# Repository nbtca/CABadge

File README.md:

# CABadge · 计协电子吧唧

基于 ESP32-S3 的开源圆屏电子徽章，面向日常佩戴与社团展示。用静态或动态壁纸表达个人喜好，通过触摸切换协会名片和小应用，也可以通过电脑或无线连接管理内容。

[固件下载](https://github.com/nbtca/CABadge/releases/tag/v1.2.0) · [PCB 工程](hardware/pcb/current/README.md) · [外壳文件](hardware/enclosure/releases/V11_V2_1_20261020/README.md) · [使用与复刻](docs/REPRODUCE.md)

<p align="center">
  
  <br />
  <sub>圆屏亮屏实物 · 计协图案</sub>
</p>

<table align="center">
  <tr>
    <td align="center"><br /><sub>侧边按键与边框</sub></td>
    <td align="center"><br /><sub>侧面轮廓</sub></td>
  </tr>
</table>

照片展示外观与亮屏效果，点击可查看原图；设计版本与验证状态见[下方版本表](#版本与资料对应)。

## 可以做什么

- **壁纸与名片**：静态图片、EAF 动态壁纸、协会名片，支持触摸浏览和切换。
- **内容管理**：通过 USB 或本地 HTTP 上传壁纸，支持 Wi-Fi、BLE 连接管理；电脑端提供原生 NBTCA Badge TOOL。
- **日常交互**：亮度设置、姿态与唤醒交互、可选 FPS 显示。
- **小应用**：Grok 表情、MC 二维地图、奶蛙矿工、重力小球，以及测试版中的 FluidBox、TimeTiles 和 BLE 心率。详见[应用说明](firmware-v7/APPS.md)。

GIF/视频需先在电脑端转换为 EAF，设备不直接播放 GIF/视频。OTA 与 BLE 传图尚未提供；功能适用版本及待测项见[已知问题](docs/KNOWN_ISSUES.md)。

## 快速入口

| 你想做什么 | 从这里开始 |
| --- | --- |
| 已有设备，安装或使用固件 | [正式固件](https://github.com/nbtca/CABadge/releases/tag/v1.2.0)、[测试固件](https://github.com/nbtca/CABadge/releases/tag/v1.3.0-rc.1)、[安装步骤](docs/REPRODUCE.md#5-烧录所选版本固件)、[无线与壁纸管理](firmware-v7/usb_screen/README.md) |
| 自己制作一块 CABadge | [V2.1 PCB](hardware/pcb/current/README.md)、[BOM 与采购资料](hardware/bom/README.md)、[V11 外壳与装配](hardware/enclosure/releases/V11_V2_1_20261020/README.md)、[完整复刻流程](docs/REPRODUCE.md) |
| 查看单个应用源码 | [应用源码目录](apps/README.md)：宝可梦、TimeTiles、Grok、MC 实时地图，各自单独保存 |
| 修改源码或参与开发 | [构建环境](docs/BUILD.md)、[开发约定](docs/DEVELOPMENT.md)、[界面架构](docs/architecture/UI_ARCHITECTURE_V7.md) |

## 版本与资料对应

固件、PCB 与外壳独立编号，请按用途选择配套文件。

| 资料 | 当前版本 | 下载或说明 |
| --- | --- | --- |
| 正式固件 | v1.2.0 / 7.9.16-eaf-transition | [正式 Release](https://github.com/nbtca/CABadge/releases/tag/v1.2.0)，工作台默认安装此版 |
| 测试固件 | v1.3.0-rc.1 / 7.9.23-timetiles-fix | [测试 Release](https://github.com/nbtca/CABadge/releases/tag/v1.3.0-rc.1)，新功能仍有待测项 |
| 公开源码 | [7.9.23-timetiles-fix](firmware-v7/version.json) | `main` 分支；[自行编译](docs/BUILD.md) |
| 当前 PCB | V2.1 GEK100 / 星火计划 | [工程说明](hardware/pcb/current/README.md)：[嘉立创EDA原生重画版](hardware/pcb/current/easyeda/CABadge_V2_1_GEK100.epro2)（2026-10-27）与 [KiCad 原工程](hardware/pcb/current/kicad/CABadge_V2_1.kicad_pro)（2026-10-20），两者不自动同步 |
| 配套外壳 | V11 一体杯壳 + V11_Button_R2 | [打印件与装配](hardware/enclosure/releases/V11_V2_1_20261020/README.md)、[SolidWorks / STEP](https://github.com/nbtca/CABadge/releases/tag/enclosure-v11-cup-button-20261029)；仅 Cup + Button，按键专项待验证 |
| 历史硬件 | V1 首板 c7c59dff，仅 KiCad | [V1 归档](hardware/pcb/archive/V1_c7c59dff/README.md)；冻结制造包属于此版 |

**自行编译请使用 `main`。** `v1.3.0-rc.1` 标签的自动 `Source code (zip)` 是旧源码快照，与其 7.9.23 固件附件不对应；[下载说明](docs/REPRODUCE.md#1-下载固件与配套硬件)解释各文件的用途。

首板 c7c59dff 的实测证据见[首板测试记录](首板测试记录.md)。V2.1 新增电源与机构、R2 按钮，以及测试固件的部分交互和长稳仍需分项验证；照片、构建或 CAD 检查不代表这些项目已全部通过。

## 硬件概览

| 部分 | 设计规格 |
| --- | --- |
| 主控与存储 | ESP32-S3R8，8 MB Octal PSRAM；W25Q128JVSIQ，16 MB Flash |
| 显示与输入 | 360 × 360 圆形 ST77916 屏幕、触摸输入、SC7A20 运动传感器 |
| 电源与充电 | SGM62117 升降压至 3.3 V；TP4056-MS 及外围供电分配、充电使能电路 |
| PCB | 直径 50 mm、四层板、名义板厚 1.6 mm |

## 如何开始复刻

1. **选定版本**：从上方表格分别选择 PCB、外壳与固件。
2. **准备器件和板子**：按[BOM 说明](hardware/bom/README.md)核对采购，从所选 PCB 工程导出并检查制造文件。
3. **焊接与上电**：按[分阶段检查表](焊接与分阶段上电检查_首板.md)调试；V2.1 新增电路的检查要求见[完整复刻说明](docs/REPRODUCE.md#4-分阶段焊接与首次上电)。
4. **安装固件**：按[烧录步骤](docs/REPRODUCE.md#5-烧录所选版本固件)核对版本、备份需要的数据并安装；已有同版设备可从这一步开始。
5. **验证与装配**：检查显示、触摸、壁纸及连接，再按[外壳装配说明](hardware/enclosure/releases/V11_V2_1_20261020/ASSEMBLY.md)完成组装。

BOM 保留 `DRAFT` 状态；V2.1 尚未附配套制造 ZIP，需从实际选用的工程导出。V1 冻结制造包不能用于制作 V2.1。具体器件、打样、分区及升级注意事项见[复刻与安装](docs/REPRODUCE.md)。

## 继续开发

板端使用 ESP-IDF / PlatformIO 与 LVGL 9.4.0，当前构建流程面向 Windows、Python 3.10+ 和 PowerShell 7。环境由 `tools/bootstrap.ps1` 安装；`CABADGE_BUILD_ROOT` 可配置工具目录，默认 `F:\CABadgeBuild`。详细操作见[构建说明](docs/BUILD.md)与[开发约定](docs/DEVELOPMENT.md)。

| 目录 | 内容 |
| --- | --- |
| `firmware-v7/` | 公开固件、UI、工作台、协议与宿主检查 |
| `hardware/` | PCB 工程、V1 归档、BOM、制造包与外壳 |
| `tools/` | 环境安装、烧录、仓库检查与发布工具 |
| `docs/` | 使用、复刻、构建、架构及已知问题 |

[完整文档索引](docs/INDEX.md) · [已知问题](docs/KNOWN_ISSUES.md) · [第三方来源与许可](docs/THIRD_PARTY.md)

## 致谢

感谢 **[嘉立创](https://www.jlc.com/)** 和 **[华秋](https://www.hqpcb.com/)** 提供的免费打板支持，也感谢组织成员 **[m1ngsama](https://github.com/m1ngsama)** 提供的 Pro 账号。这些支持为本项目的开发提供了极大的帮助。

## 许可

本项目原创内容采用 [MIT License](LICENSE)。第三方字体、库、模型和素材仍遵循各自许可；字体许可见 [FONT-LICENSE.txt](firmware-v7/ui/FONT-LICENSE.txt)。

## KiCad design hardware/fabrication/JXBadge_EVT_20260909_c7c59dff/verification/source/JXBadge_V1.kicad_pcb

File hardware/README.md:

# CABadge 硬件资料

**当前板卡：V2.1 GEK100 / 星火计划。** [打开当前版本说明](pcb/current/README.md)，选择 [KiCad 工程](pcb/current/kicad/CABadge_V2_1.kicad_pro)或[嘉立创EDA工程](pcb/current/easyeda/CABadge_V2_1_GEK100.epro2)。

| 版本 | 格式与来源 | 入口 |
| --- | --- | --- |
| 当前 V2.1 | KiCad 保留 2026-10-20 原文件；EDA 替换为 2026-10-27 原生重画工程 | [pcb/current](pcb/current/README.md) |
| V1 首板 c7c59dff | 仅 KiCad，连同原理图、项目库和模型归档 | [pcb/archive/V1_c7c59dff](pcb/archive/V1_c7c59dff/README.md) |

今天的重画工程属于 V2.1 的 EDA 格式更新，五张原理图复用、PCB 原生重画。旧的 KiCad 转换版 EDA 已从当前仓库文件中移除，过往版本由 Git 历史保留。

## 目录与使用范围

| 目录 | 内容 | 版本说明 |
| --- | --- | --- |
| [pcb/current](pcb/current/README.md) | 当前 V2.1 的 KiCad、EDA、预览与校验信息 | 后续 V2.1 工程更新使用固定路径 |
| [V1 归档](pcb/archive/V1_c7c59dff/README.md) | 首板 KiCad 源文件、符号库、封装库和本地模型 | 历史源文件；与冻结制造快照分别保存 |
| [bom](bom/README.md) | 原 BOM、采购表、料号列表、版本对比及交互式 BOM | CSV 为已有 V1 / V2.1 KiCad 用量记录；交互式 BOM 为 V1 快照，元器件核对已停止 |
| [冻结制造包](fabrication/JXBadge_EVT_20260909_c7c59dff/下单说明.md) | 首板 Gerber、钻孔、钢网及导出核验源快照 | 本次保持路径与全部文件字节不变 |
| [V11 外壳](enclosure/releases/V11_V2_1_20261020/README.md) | V2.1 配套打印件、装配模型与说明；当前按钮为 R2 | 2026-10-29 按实际装配更新为 Cup + Button 两件打印方案，杯壳与 R2 按帽几何保持；几何检查对应说明中的 KiCad PCB；[V6](enclosure/releases/V6_20260930/README.md)为历史外壳 |

## 采购、装配与验证

当前 EDA 中 J1 为 AFC07-S18ECC-00 / C2840708，按用户决定保留原封装；U3 保持 SC7A20TR / C5126709。BOM 和商城器件库核对已停止，旧 CSV 未在本次整理中重新核对或改料。

电池沿用用户提供的 450 mAh、42×30×4 mm，正负线直接焊接、J3 不装。具体版本和历史装配说明见 [BOM 说明](bom/README.md)、[J1 更正](../docs/J1-CONNECTOR.md)和[V1 历史记录](pcb/archive/V1_c7c59dff/README.md#电池与屏幕连接器)。

[焊接与分阶段上电检查](../焊接与分阶段上电检查_首板.md)保留其设计核对依据；[首板测试记录](../首板测试记录.md)保留实物反馈与历史失败。工程归档、文件校验及已有 CAD 检查不代替 V2.1 新板的制造、机械和实物功能验收。

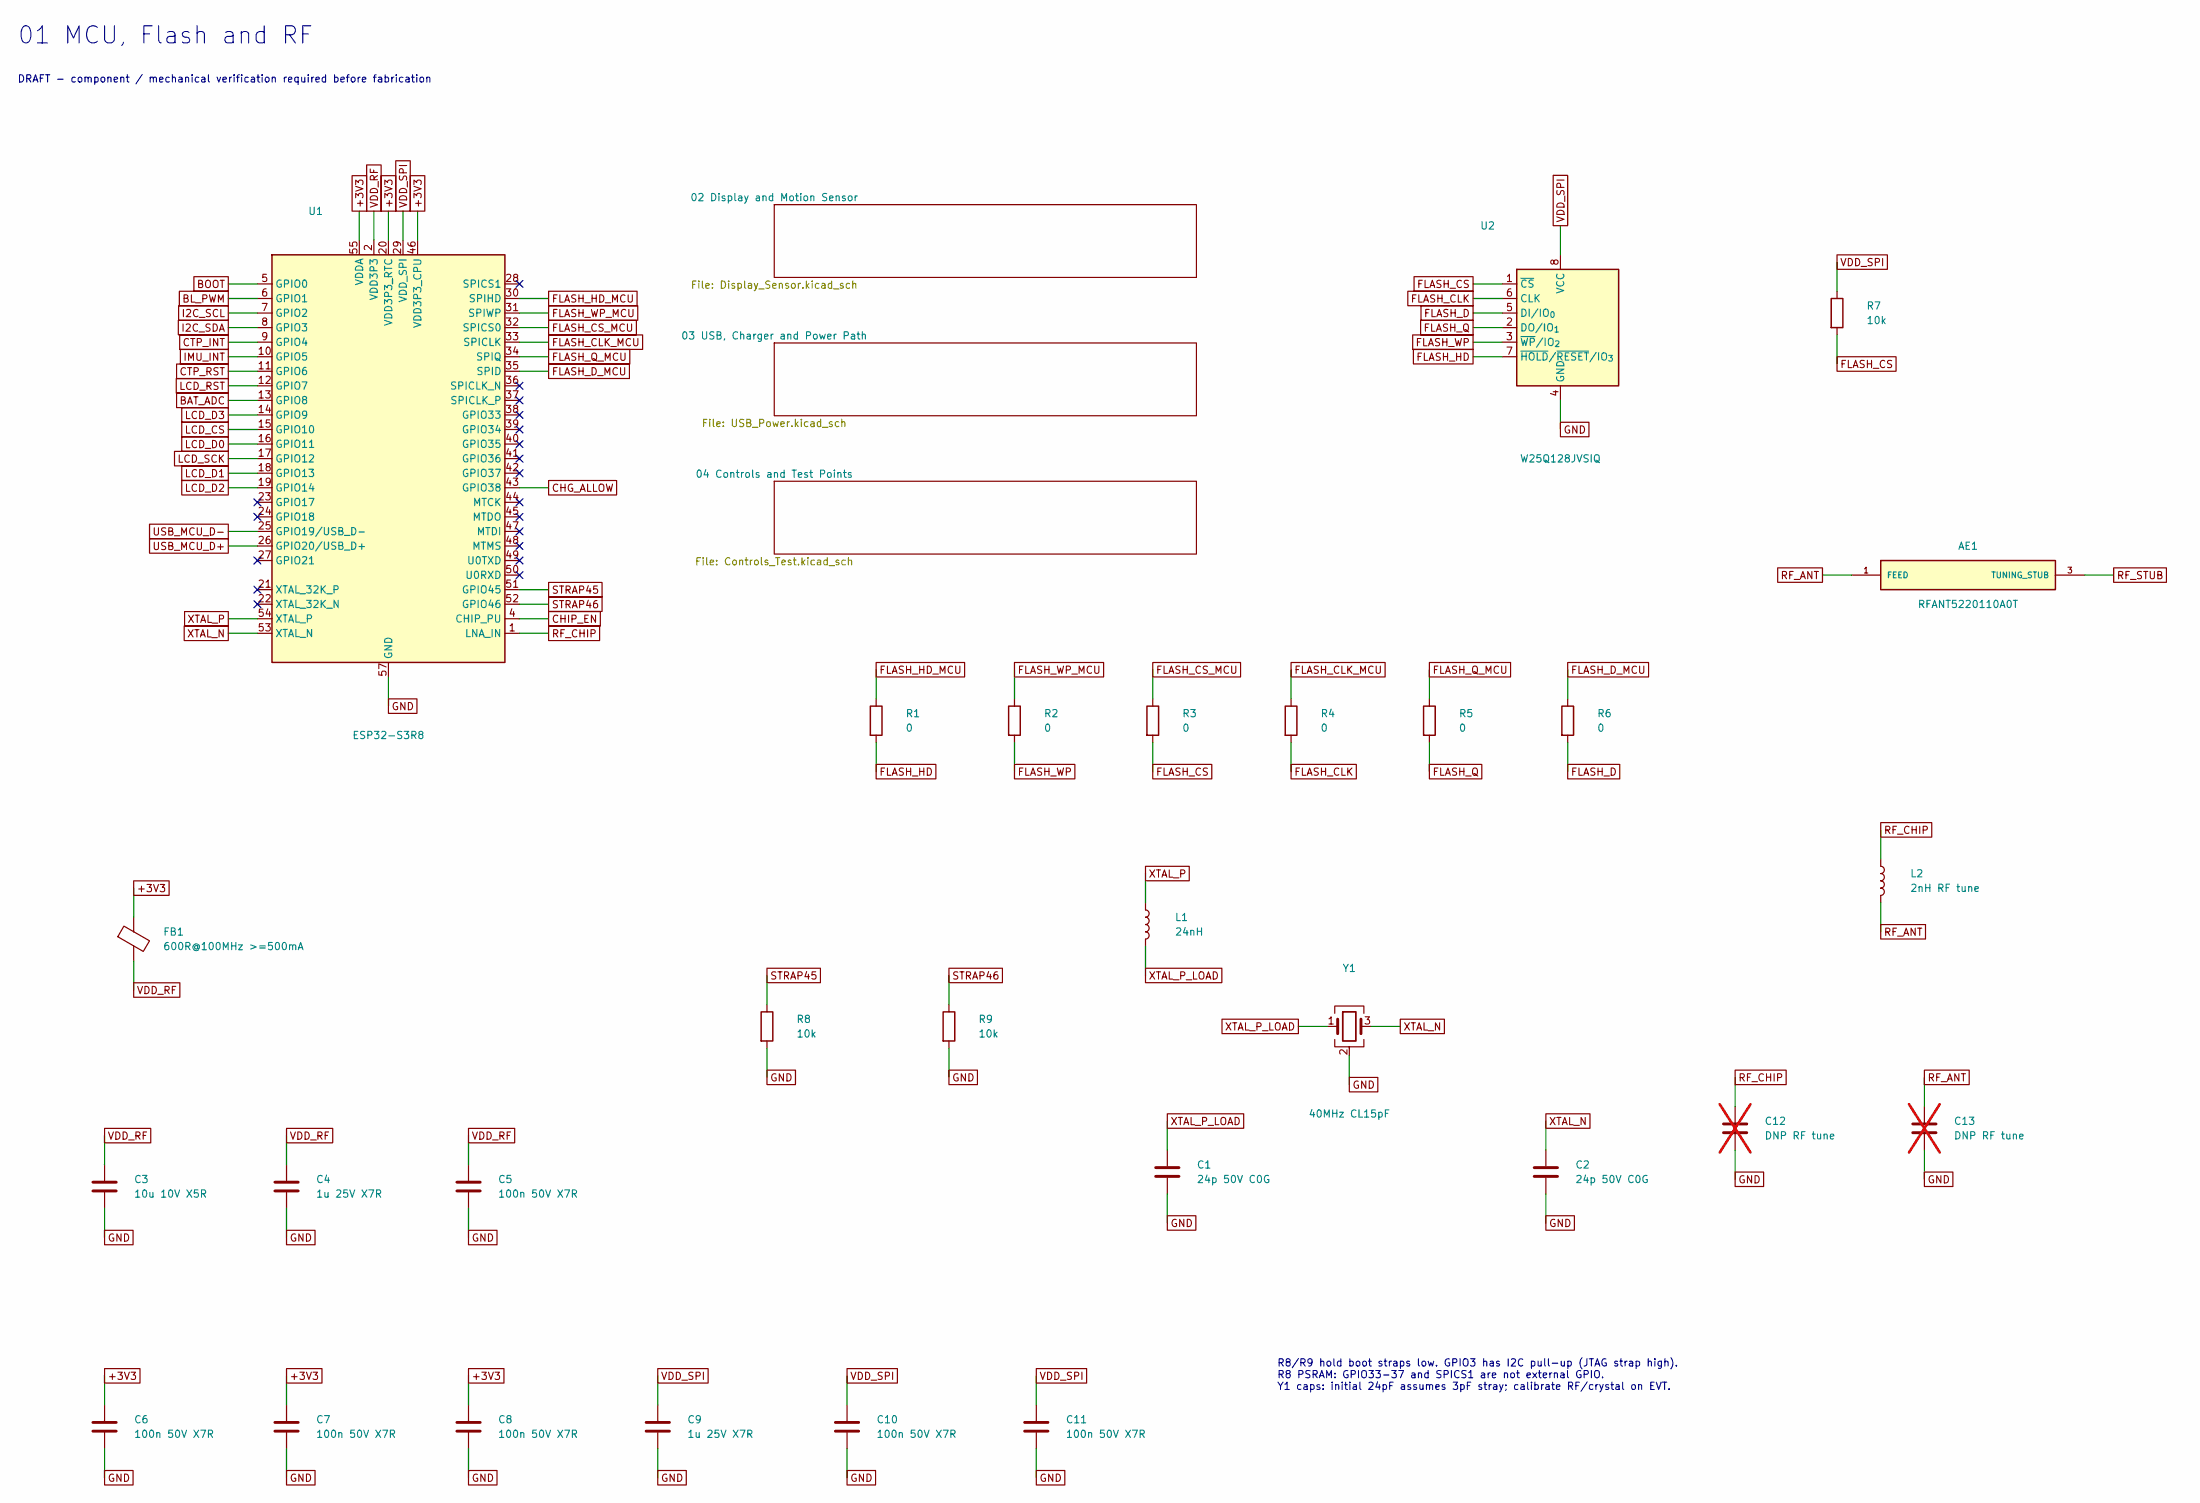
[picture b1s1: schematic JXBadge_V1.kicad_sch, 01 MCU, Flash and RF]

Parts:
AE1: RFANT5220110A0T; RFANT5220110A0T_C127611; MPN RFANT5220110A0T; LCSC C127611
C1, C2: 24p 50V C0G; 0603CG240J500NT_C1654; MPN 0603CG240J500NT; LCSC C1654
C3: 10u 10V X5R; CL10A106KP8NNNC_C19702; MPN CL10A106KP8NNNC; LCSC C19702
C4, C9: 1u 25V X7R; CL10B105KA8NNNC_C29936; MPN CL10B105KA8NNNC; LCSC C29936
C5, C6, C7, C8, C10, C11: 100n 50V X7R; CC0603KRX7R9BB104_C14663; MPN CC0603KRX7R9BB104; LCSC C14663
C12, C13: DNP RF tune; C_0201_0603Metric; MPN DNP RF tune; not fitted
FB1: 600R@100MHz >=500mA; BLM18AG601SN1D_C19330; MPN BLM18AG601SN1D; LCSC C19330
L1: 24nH; LQG15WZ24NH02D_C1012734; MPN LQG15WZ24NH02D; LCSC C1012734
L2: 2nH RF tune; LQP03TN2N0B02D_C86125; MPN LQP03TN2N0B02D; LCSC C86125
R1, R2, R3, R4, R5, R6: 0; 0603WAF0000T5E_C21189; MPN 0603WAF0000T5E; LCSC C21189
R7, R8, R9: 10k; 0603WAF1002T5E_C25804; MPN 0603WAF1002T5E; LCSC C25804
U1: ESP32-S3R8; ESP32-S3_R8__C2913194; MPN ESP32-S3R8; LCSC C2913194
U2: W25Q128JVSIQ; W25Q128JVSIQTR_C97521; MPN W25Q128JVSIQ; LCSC C97521
Y1: 40MHz CL15pF; TAXM40M4ZHBCDT2T_C424432; MPN TAXM40M4ZHBCDT2T; LCSC C424432

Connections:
+3V3: C6.1, C7.1, C8.1, FB1.1, U1.20 (VDD3P3_RTC), U1.46 (VDD3P3_CPU), U1.55 (VDDA), U1.56 (VDDA); also elsewhere on the board
BAT_ADC: U1.13 (GPIO8); also elsewhere on the board
BL_PWM: U1.6 (GPIO1); also elsewhere on the board
BOOT: U1.5 (GPIO0); also elsewhere on the board
CHG_ALLOW: U1.43 (GPIO38); also elsewhere on the board
CHIP_EN: U1.4 (CHIP_PU); also elsewhere on the board
CTP_INT: U1.9 (GPIO4); also elsewhere on the board
CTP_RST: U1.11 (GPIO6); also elsewhere on the board
FLASH_CLK: R4.2, U2.6 (CLK)
FLASH_CLK_MCU: R4.1, U1.33 (SPICLK)
FLASH_CS: R3.2, R7.2, U2.1 (~CS)
FLASH_CS_MCU: R3.1, U1.32 (SPICS0)
FLASH_D: R6.2, U2.5 (DI/IO_{0})
FLASH_D_MCU: R6.1, U1.35 (SPID)
FLASH_HD: R1.2, U2.7 (~HOLD/~RESET/IO_{3})
FLASH_HD_MCU: R1.1, U1.30 (SPIHD)
FLASH_Q: R5.2, U2.2 (DO/IO_{1})
FLASH_Q_MCU: R5.1, U1.34 (SPIQ)
FLASH_WP: R2.2, U2.3 (~WP/IO_{2})
FLASH_WP_MCU: R2.1, U1.31 (SPIWP)
GND: C1.2, C2.2, C3.2, C4.2, C5.2, C6.2, C7.2, C8.2, C9.2, C10.2, C11.2, C12.2, C13.2, R8.2, R9.2, U1.57 (GND), U2.4 (GND), Y1.2 (G), Y1.4 (G); also elsewhere on the board
I2C_SCL: U1.7 (GPIO2); also elsewhere on the board
I2C_SDA: U1.8 (GPIO3); also elsewhere on the board
IMU_INT: U1.10 (GPIO5); also elsewhere on the board
LCD_CS: U1.15 (GPIO10); also elsewhere on the board
LCD_D0: U1.16 (GPIO11); also elsewhere on the board
LCD_D1: U1.18 (GPIO13); also elsewhere on the board
LCD_D2: U1.19 (GPIO14); also elsewhere on the board
LCD_D3: U1.14 (GPIO9); also elsewhere on the board
LCD_RST: U1.12 (GPIO7); also elsewhere on the board
LCD_SCK: U1.17 (GPIO12); also elsewhere on the board
RF_ANT: AE1.1 (FEED), C13.1, L2.2
RF_CHIP: C12.1, L2.1, U1.1 (LNA_IN)
RF_STUB: AE1.3 (TUNING_STUB)
STRAP45: R8.1, U1.51 (GPIO45)
STRAP46: R9.1, U1.52 (GPIO46)
USB_MCU_D+: U1.26 (GPIO20/USB_D+); also elsewhere on the board
USB_MCU_D-: U1.25 (GPIO19/USB_D-); also elsewhere on the board
VDD_RF: C3.1, C4.1, C5.1, FB1.2, U1.2 (VDD3P3), U1.3 (VDD3P3)
VDD_SPI: C9.1, C10.1, C11.1, R7.1, U1.29 (VDD_SPI), U2.8 (VCC)
XTAL_N: C2.1, U1.53 (XTAL_N), Y1.3
XTAL_P: L1.1, U1.54 (XTAL_P)
XTAL_P_LOAD: C1.1, L1.2, Y1.1

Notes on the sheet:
01 MCU, Flash and RF
DRAFT - component / mechanical verification required before fabrication
R8/R9 hold boot straps low. GPIO3 has I2C pull-up (JTAG strap high). R8 PSRAM: GPIO33-37 and SPICS1 are not external GPIO. Y1 caps: initial 24pF assumes 3pF stray; calibrate RF/crystal on EVT.

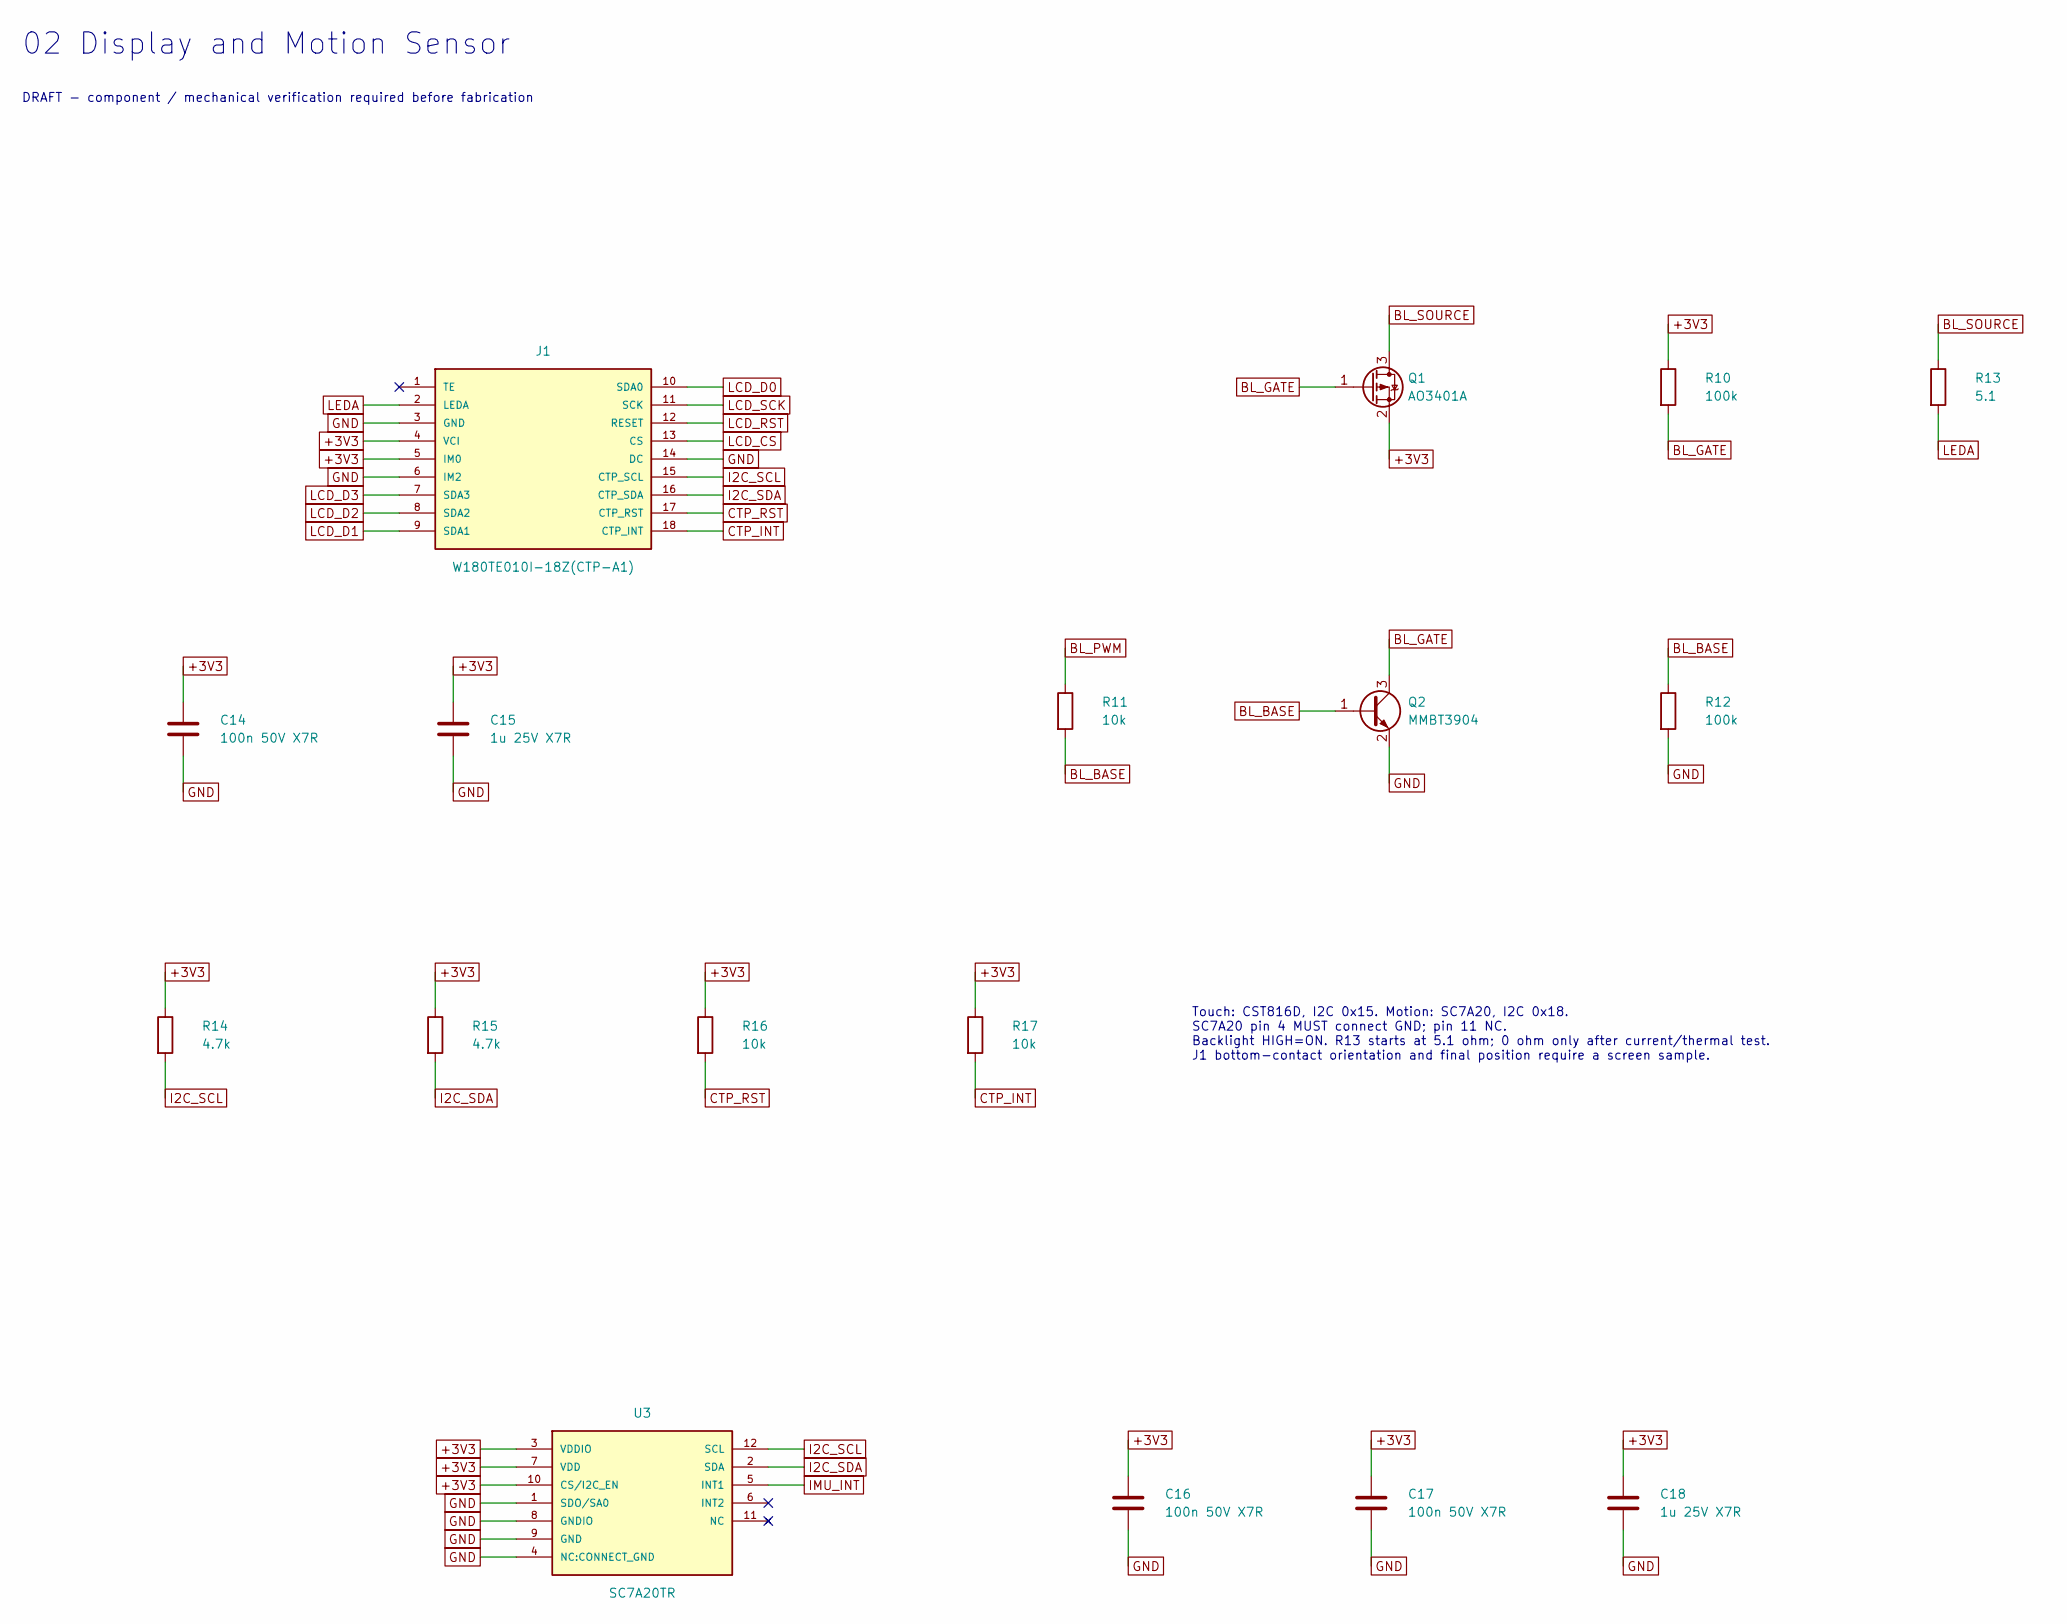
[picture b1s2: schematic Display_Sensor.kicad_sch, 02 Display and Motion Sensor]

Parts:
C14, C16, C17: 100n 50V X7R; CC0603KRX7R9BB104_C14663; MPN CC0603KRX7R9BB104; LCSC C14663
C15, C18: 1u 25V X7R; CL10B105KA8NNNC_C29936; MPN CL10B105KA8NNNC; LCSC C29936
J1: W180TE010I-18Z(CTP-A1); FPC-05F-18PH20_C2856802; MPN FPC-05F-18PH20; LCSC C2856802
Q1: AO3401A; AO3401A_C15127; MPN AO3401A; LCSC C15127
Q2: MMBT3904; MMBT3904_215_C426835; MPN MMBT3904,215; LCSC C426835
R10, R12: 100k; 0603WAF1003T5E_C25803; MPN 0603WAF1003T5E; LCSC C25803
R11, R16, R17: 10k; 0603WAF1002T5E_C25804; MPN 0603WAF1002T5E; LCSC C25804
R13: 5.1; 0603WAF510KT5E_C25197; MPN 0603WAF510KT5E; LCSC C25197
R14, R15: 4.7k; 0603WAF4701T5E_C23162; MPN 0603WAF4701T5E; LCSC C23162
U3: SC7A20TR; SC7A20TR_C5126709_C5126709; MPN SC7A20TR; LCSC C5126709

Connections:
+3V3: C14.1, C15.1, C16.1, C17.1, C18.1, J1.4 (VCI), J1.5 (IM0), Q1.2 (S), R10.1, R14.1, R15.1, R16.1, R17.1, U3.3 (VDDIO), U3.7 (VDD), U3.10 (CS/I2C_EN); also elsewhere on the board
BL_BASE: Q2.1 (B), R11.2, R12.1
BL_GATE: Q1.1 (G), Q2.3 (C), R10.2
BL_PWM: R11.1; also elsewhere on the board
BL_SOURCE: Q1.3 (D), R13.1
CTP_INT: J1.18 (CTP_INT), R17.2; also elsewhere on the board
CTP_RST: J1.17 (CTP_RST), R16.2; also elsewhere on the board
GND: C14.2, C15.2, C16.2, C17.2, C18.2, J1.3 (GND), J1.6 (IM2), J1.14 (DC), Q2.2 (E), R12.2, U3.1 (SDO/SA0), U3.4 (NC:CONNECT_GND), U3.8 (GNDIO), U3.9 (GND); also elsewhere on the board
I2C_SCL: J1.15 (CTP_SCL), R14.2, U3.12 (SCL); also elsewhere on the board
I2C_SDA: J1.16 (CTP_SDA), R15.2, U3.2 (SDA); also elsewhere on the board
IMU_INT: U3.5 (INT1); also elsewhere on the board
LCD_CS: J1.13 (CS); also elsewhere on the board
LCD_D0: J1.10 (SDA0); also elsewhere on the board
LCD_D1: J1.9 (SDA1); also elsewhere on the board
LCD_D2: J1.8 (SDA2); also elsewhere on the board
LCD_D3: J1.7 (SDA3); also elsewhere on the board
LCD_RST: J1.12 (RESET); also elsewhere on the board
LCD_SCK: J1.11 (SCK); also elsewhere on the board
LEDA: J1.2 (LEDA), R13.2

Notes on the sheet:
02 Display and Motion Sensor
DRAFT - component / mechanical verification required before fabrication
Touch: CST816D, I2C 0x15. Motion: SC7A20, I2C 0x18. SC7A20 pin 4 MUST connect GND; pin 11 NC. Backlight HIGH=ON. R13 starts at 5.1 ohm; 0 ohm only after current/thermal test. J1 bottom-contact orientation and final position require a screen sample.

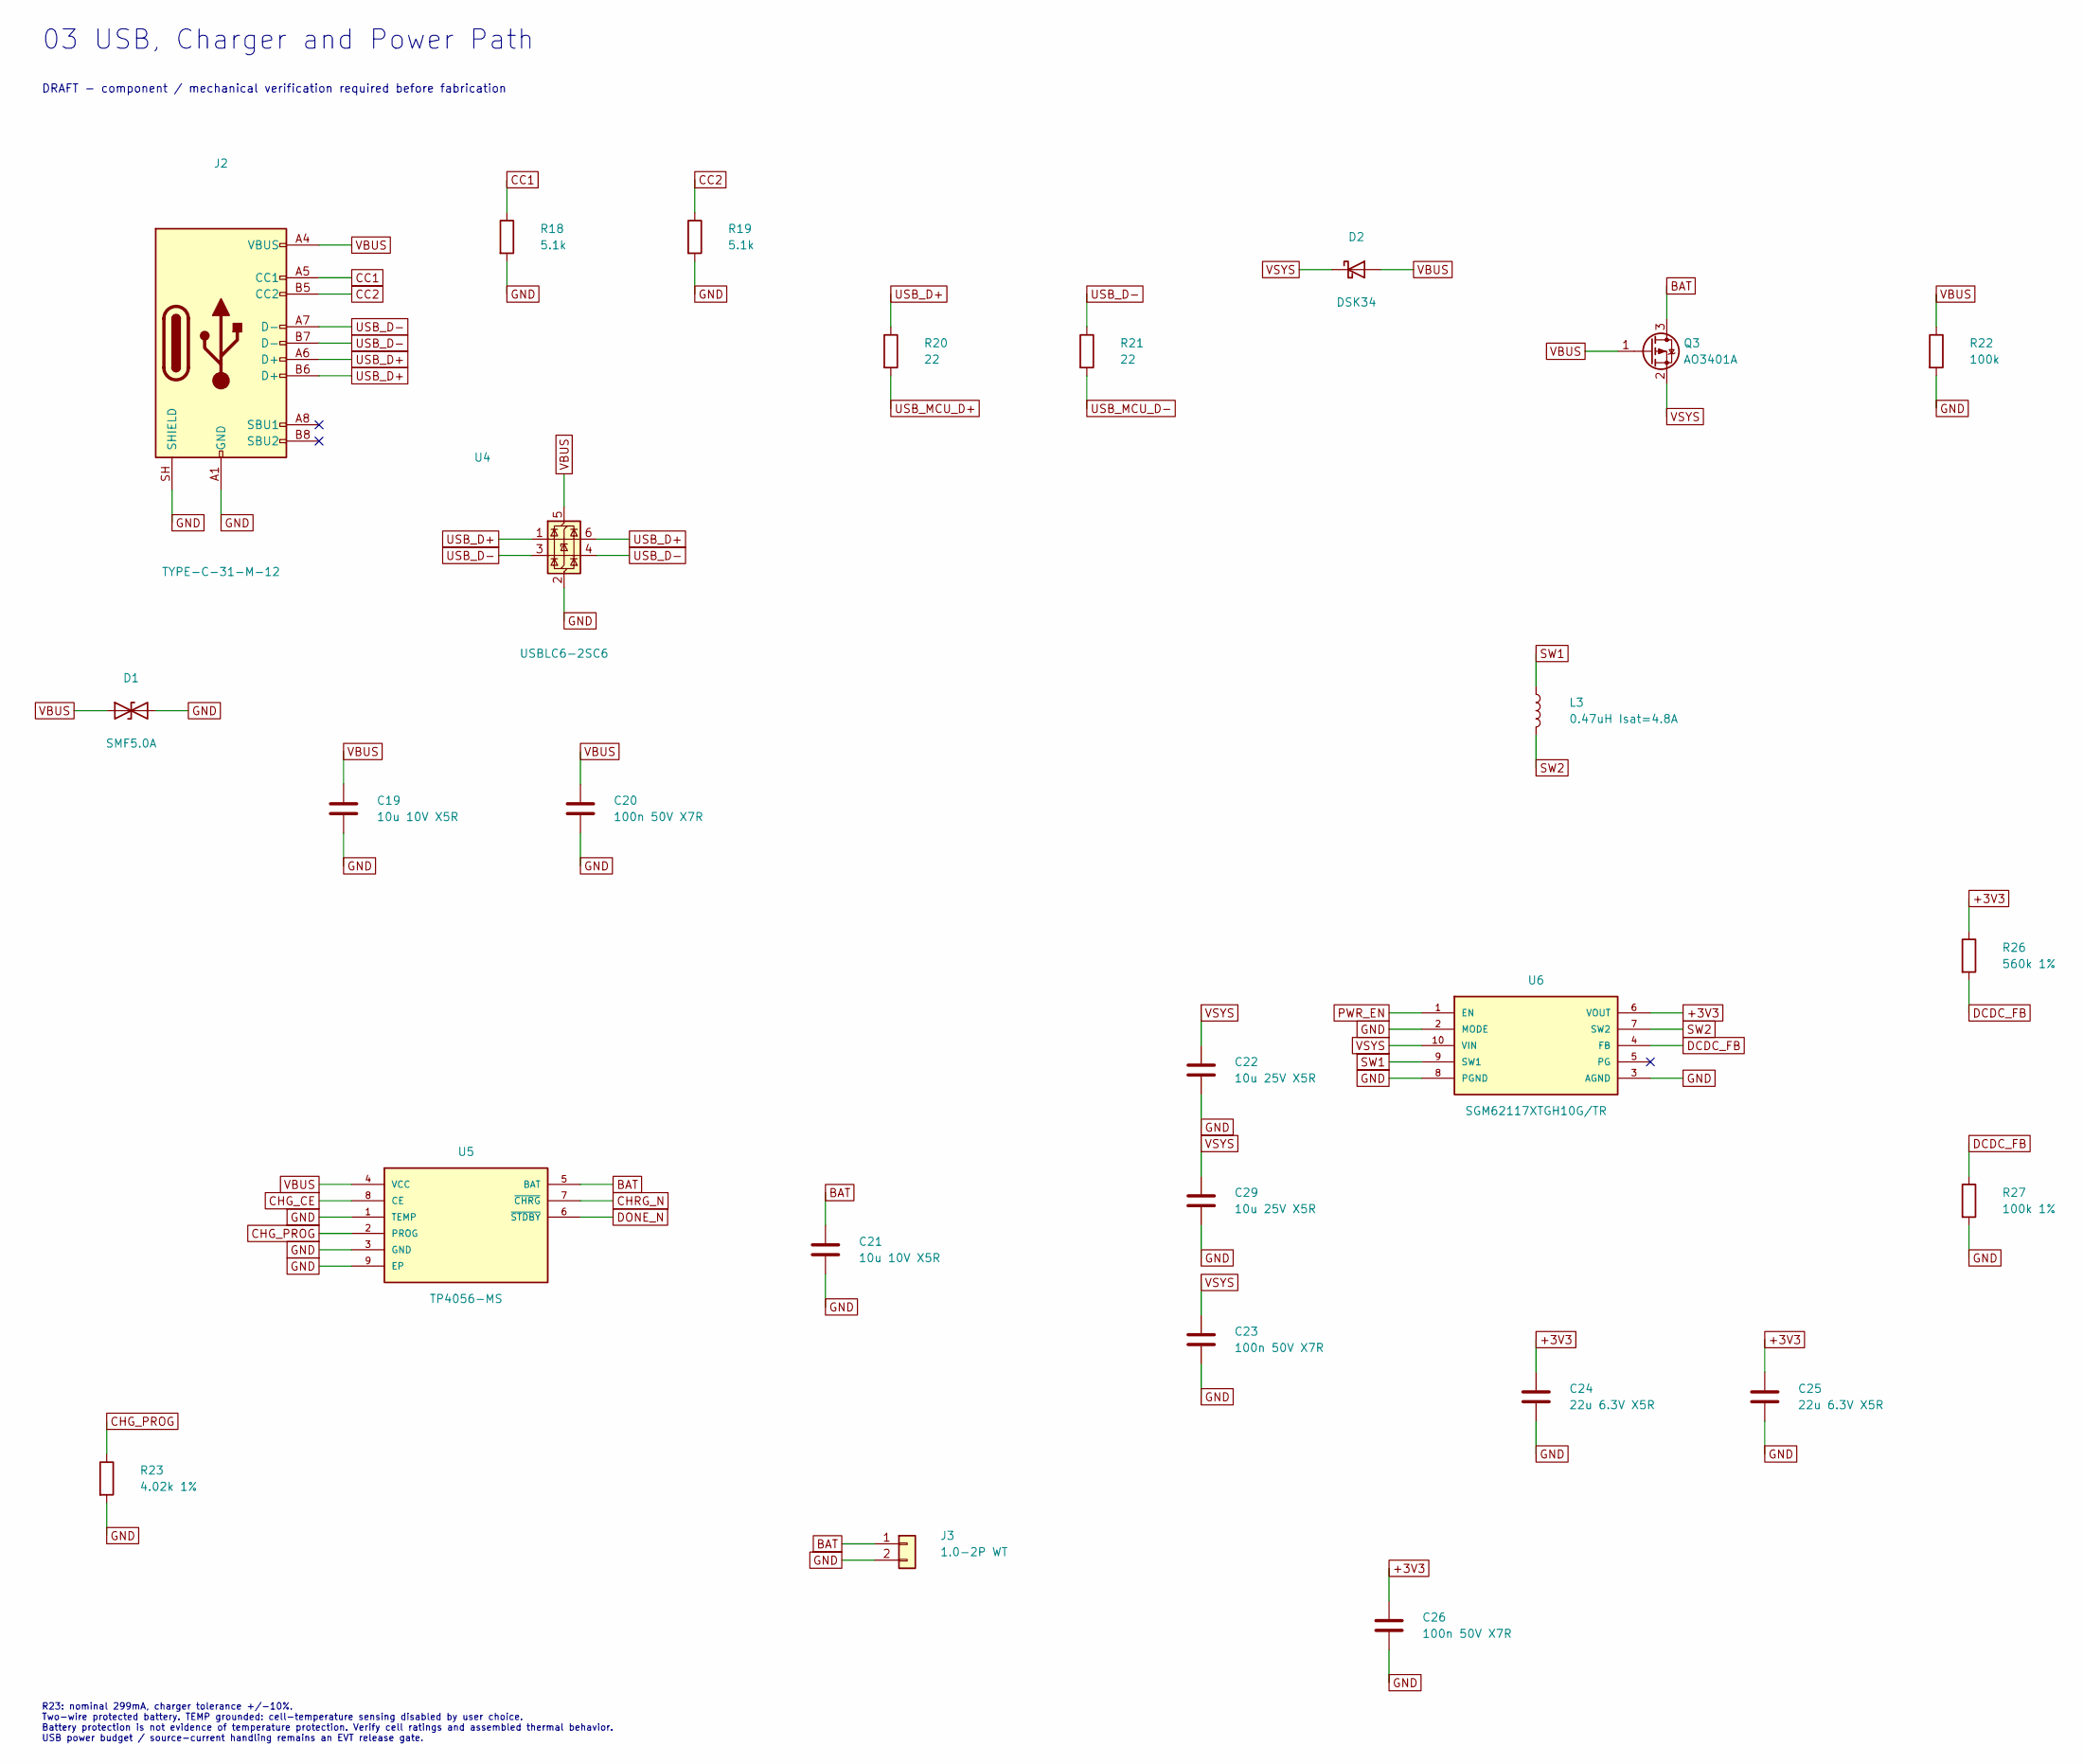
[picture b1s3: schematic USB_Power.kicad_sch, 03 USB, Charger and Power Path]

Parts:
C19, C21: 10u 10V X5R; CL10A106KP8NNNC_C19702; MPN CL10A106KP8NNNC; LCSC C19702
C20, C23, C26: 100n 50V X7R; CC0603KRX7R9BB104_C14663; MPN CC0603KRX7R9BB104; LCSC C14663
C22, C29: 10u 25V X5R; CL21A106KAYNNNE_C15850; MPN CL21A106KAYNNNE; LCSC C15850
C24, C25: 22u 6.3V X5R; CL10A226MQ8NRNC_C59461; MPN CL10A226MQ8NRNC; LCSC C59461
D1: SMF5.0A; SMF5_0A_C151296; MPN SMF5.0A; LCSC C151296
D2: DSK34; DSK34_C727076_C727076; MPN DSK34; LCSC C727076
J2: TYPE-C-31-M-12; TYPE-C-31-M-12_C165948; MPN TYPE-C-31-M-12; LCSC C165948
J3: 1.0-2P WT; 1_0-2P_WT_C2906268; MPN 1.0-2P WT; LCSC C2906268
L3: 0.47uH Isat=4.8A; DFE201610E-R47M_P2_C269773; MPN DFE201610E-R47M=P2; LCSC C269773
Q3: AO3401A; AO3401A_C15127; MPN AO3401A; LCSC C15127
R18, R19: 5.1k; 0603WAF5101T5E_C23186; MPN 0603WAF5101T5E; LCSC C23186
R20, R21: 22; 0603WAF220JT5E_C23345; MPN 0603WAF220JT5E; LCSC C23345
R22: 100k; 0603WAF1003T5E_C25803; MPN 0603WAF1003T5E; LCSC C25803
R23: 4.02k 1%; 0603WAF4021T5E_C23040_C23040; MPN 0603WAF4021T5E; LCSC C23040
R26: 560k 1%; 0603WAF5603T5E_C23203; MPN 0603WAF5603T5E; LCSC C23203
R27: 100k 1%; 0603WAF1003T5E_C25803; MPN 0603WAF1003T5E; LCSC C25803
U4: USBLC6-2SC6; USBLC6-2SC6_C7519; MPN USBLC6-2SC6; LCSC C7519
U5: TP4056-MS; TP4056-MS_C7473158; MPN TP4056-MS; LCSC C7473158
U6: SGM62117XTGH10G/TR; SGM62117XTGH10G_TR_C5152031; MPN SGM62117XTGH10G/TR; LCSC C5152031

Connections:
+3V3: C24.1, C25.1, C26.1, R26.1, U6.6 (VOUT); also elsewhere on the board
BAT: C21.1, J3.1, Q3.3 (D), U5.5 (BAT); also elsewhere on the board
CC1: J2.A5 (CC1), R18.1
CC2: J2.B5 (CC2), R19.1
CHG_CE: U5.8 (CE); also elsewhere on the board
CHG_PROG: R23.1, U5.2 (PROG)
CHRG_N: U5.7 (~CHRG); also elsewhere on the board
DCDC_FB: R26.2, R27.1, U6.4 (FB)
DONE_N: U5.6 (~STDBY); also elsewhere on the board
GND: C19.2, C20.2, C21.2, C22.2, C23.2, C24.2, C25.2, C26.2, C29.2, D1.2 (A2), J2.A1 (GND), J2.A12 (GND), J2.B1 (GND), J2.B12 (GND), J2.SH (SHIELD), J3.2, R18.2, R19.2, R22.2, R23.2, R27.2, U4.2 (GND), U5.1 (TEMP), U5.3 (GND), U5.9 (EP), U6.2 (MODE), U6.3 (AGND), U6.8 (PGND); also elsewhere on the board
PWR_EN: U6.1 (EN); also elsewhere on the board
SW1: L3.1, U6.9 (SW1)
SW2: L3.2, U6.7 (SW2)
USB_D+: J2.A6 (D+), J2.B6 (D+), R20.1, U4.1 (I/O1), U4.6 (I/O1); also elsewhere on the board
USB_D-: J2.A7 (D-), J2.B7 (D-), R21.1, U4.3 (I/O2), U4.4 (I/O2); also elsewhere on the board
USB_MCU_D+: R20.2; also elsewhere on the board
USB_MCU_D-: R21.2; also elsewhere on the board
VBUS: C19.1, C20.1, D1.1 (A1), D2.2 (A), J2.A4 (VBUS), J2.A9 (VBUS), J2.B4 (VBUS), J2.B9 (VBUS), Q3.1 (G), R22.1, U4.5 (VBUS), U5.4 (VCC); also elsewhere on the board
VSYS: C22.1, C23.1, C29.1, D2.1 (K), Q3.2 (S), U6.10 (VIN); also elsewhere on the board

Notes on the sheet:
03 USB, Charger and Power Path
DRAFT - component / mechanical verification required before fabrication
R23: nominal 299mA, charger tolerance +/-10%. Two-wire protected battery. TEMP grounded: cell-temperature sensing disabled by user choice. Battery protection is not evidence of temperature protection. Verify cell ratings and assembled thermal behavior. USB power budget / source-current handling rem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

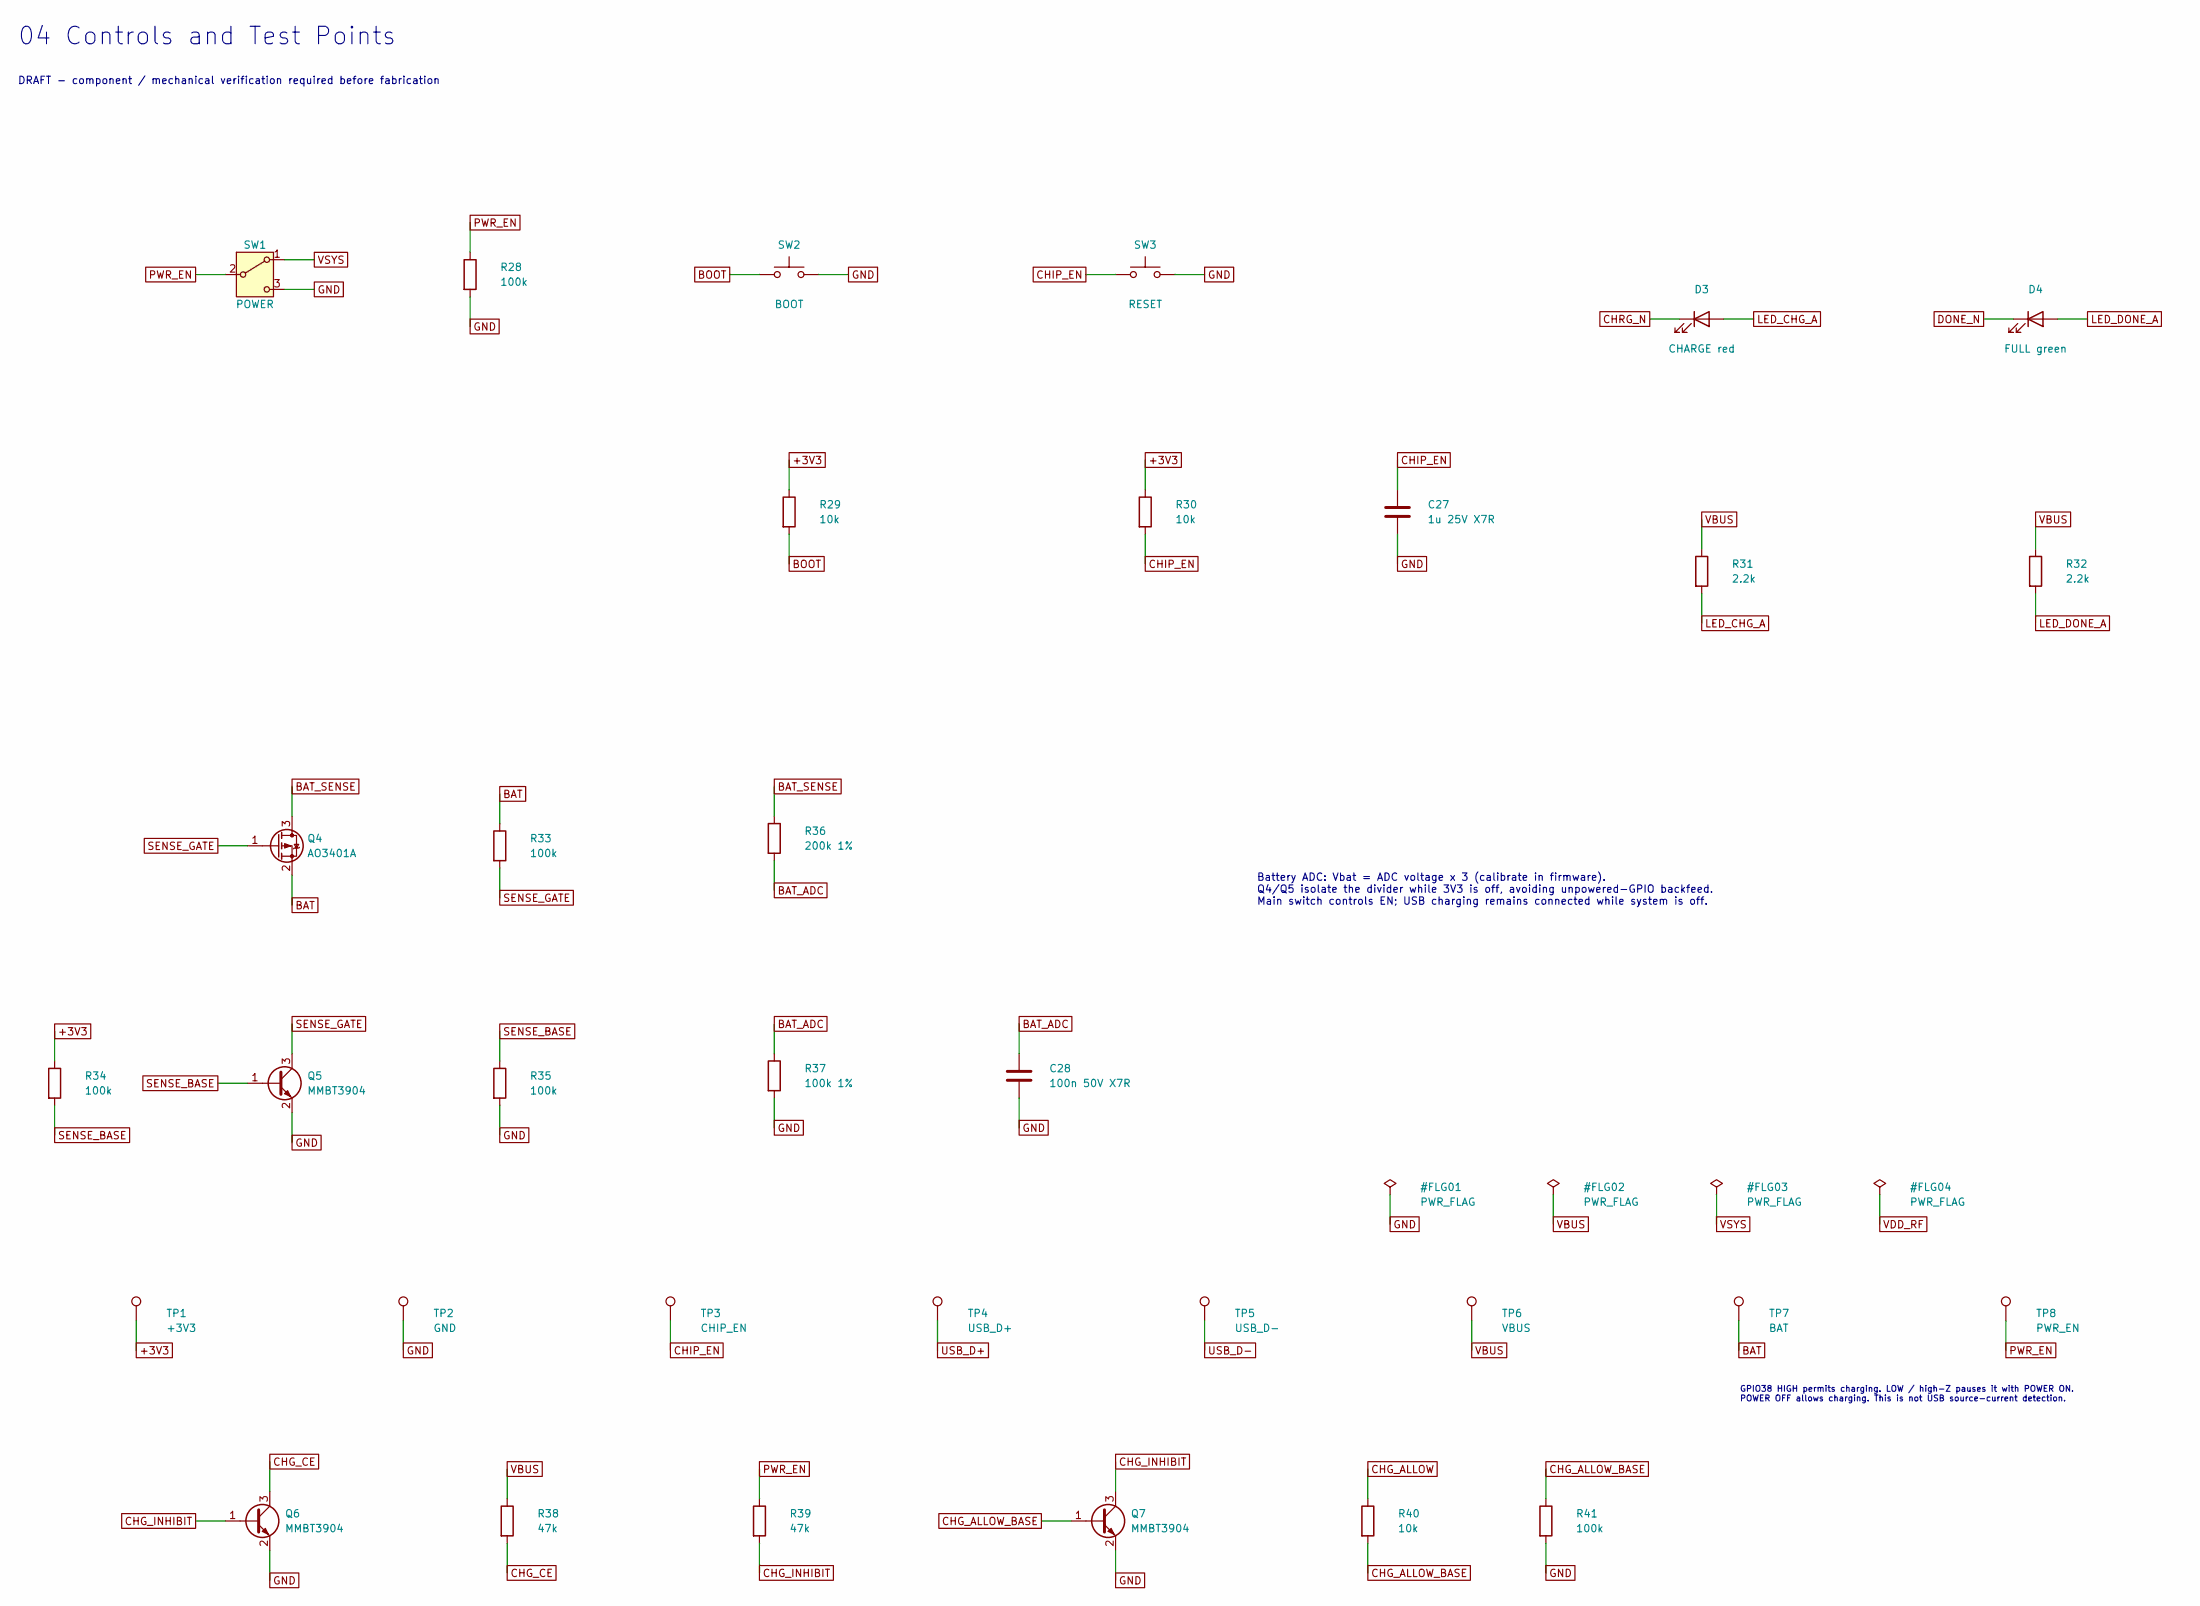
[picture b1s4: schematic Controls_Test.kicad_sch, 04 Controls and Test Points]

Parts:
C27: 1u 25V X7R; CL10B105KA8NNNC_C29936; MPN CL10B105KA8NNNC; LCSC C29936
C28: 100n 50V X7R; CC0603KRX7R9BB104_C14663; MPN CC0603KRX7R9BB104; LCSC C14663
D3: CHARGE red; KT-0603R_C2286; MPN KT-0603R; LCSC C2286
D4: FULL green; 19-217_GHC-YR1S2_3T_C72043; MPN 19-217/GHC-YR1S2/3T; LCSC C72043
Q4: AO3401A; AO3401A_C15127; MPN AO3401A; LCSC C15127
Q5, Q6, Q7: MMBT3904; MMBT3904_215_C426835; MPN MMBT3904,215; LCSC C426835
R28, R33, R34, R35, R41: 100k; 0603WAF1003T5E_C25803; MPN 0603WAF1003T5E; LCSC C25803
R29, R30, R40: 10k; 0603WAF1002T5E_C25804; MPN 0603WAF1002T5E; LCSC C25804
R31, R32: 2.2k; 0603WAF2201T5E_C4190; MPN 0603WAF2201T5E; LCSC C4190
R36: 200k 1%; 0603WAF2003T5E_C25811; MPN 0603WAF2003T5E; LCSC C25811
R37: 100k 1%; 0603WAF1003T5E_C25803; MPN 0603WAF1003T5E; LCSC C25803
R38, R39: 47k; 0603WAF4702T5E_C25819; MPN 0603WAF4702T5E; LCSC C25819
SW1: POWER; JS102011SAQN_C221660; MPN JS102011SAQN; LCSC C221660
SW2: BOOT; HX-2X4X3_5CA-2_5N_C49234137; MPN HX-2X4X3.5CA-2.5N; LCSC C49234137
SW3: RESET; HX-2X4X3_5CA-2_5N_C49234137; MPN HX-2X4X3.5CA-2.5N; LCSC C49234137
TP1: +3V3; TestPoint_Pad_D1.0mm; MPN PCB test pad
TP2: GND; TestPoint_Pad_D1.0mm; MPN PCB test pad
TP3: CHIP_EN; TestPoint_Pad_D1.0mm; MPN PCB test pad
TP4: USB_D+; USB_TestPoint_D0.4mm; MPN PCB test pad
TP5: USB_D-; USB_TestPoint_D0.4mm; MPN PCB test pad
TP6: VBUS; TestPoint_Pad_D1.0mm; MPN PCB test pad
TP7: BAT; TestPoint_Pad_D1.0mm; MPN PCB test pad
TP8: PWR_EN; TestPoint_Pad_D1.0mm; MPN PCB test pad

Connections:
+3V3: R29.1, R30.1, R34.1, TP1.1; also elsewhere on the board
BAT: Q4.2 (S), R33.1, TP7.1; also elsewhere on the board
BAT_ADC: C28.1, R36.2, R37.1; also elsewhere on the board
BAT_SENSE: Q4.3 (D), R36.1
BOOT: R29.2, SW2.1; also elsewhere on the board
CHG_ALLOW: R40.1; also elsewhere on the board
CHG_ALLOW_BASE: Q7.1 (B), R40.2, R41.1
CHG_CE: Q6.3 (C), R38.2; also elsewhere on the board
CHG_INHIBIT: Q6.1 (B), Q7.3 (C), R39.2
CHIP_EN: C27.1, R30.2, SW3.1, TP3.1; also elsewhere on the board
CHRG_N: D3.1 (K); also elsewhere on the board
DONE_N: D4.1 (K); also elsewhere on the board
GND: C27.2, C28.2, Q5.2 (E), Q6.2 (E), Q7.2 (E), R28.2, R35.2, R37.2, R41.2, SW1.3 (C), SW2.2, SW3.2, TP2.1; also elsewhere on the board
LED_CHG_A: D3.2 (A), R31.2
LED_DONE_A: D4.2 (A), R32.2
PWR_EN: R28.1, R39.1, SW1.2 (B), TP8.1; also elsewhere on the board
SENSE_BASE: Q5.1 (B), R34.2, R35.1
SENSE_GATE: Q4.1 (G), Q5.3 (C), R33.2
USB_D+: TP4.1; also elsewhere on the board
USB_D-: TP5.1; also elsewhere on the board
VBUS: R31.1, R32.1, R38.1, TP6.1; also elsewhere on the board
VSYS: SW1.1 (A); also elsewhere on the board

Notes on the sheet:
04 Controls and Test Points
DRAFT - component / mechanical verification required before fabrication
Battery ADC: Vbat = ADC voltage x 3 (calibrate in firmware). Q4/Q5 isolate the divider while 3V3 is off, avoiding unpowered-GPIO backfeed. Main switch controls EN; USB charging remains connected while system is off.
GPIO38 HIGH permits charging. LOW / high-Z pauses it with POWER ON. POWER OFF allows charging. This is not USB source-current detection.
